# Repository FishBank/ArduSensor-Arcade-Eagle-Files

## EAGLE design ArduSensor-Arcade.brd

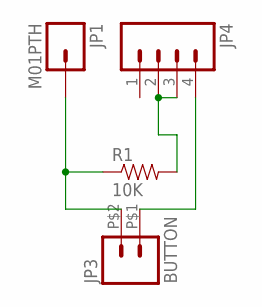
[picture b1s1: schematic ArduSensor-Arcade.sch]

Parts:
JP1: M01PTH; 1X01
JP3: BUTTON; 1X02_BIG
JP4: M04PTH; 1X04
R1: 10K; AXIAL-0.3

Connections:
unnamed: JP1.1, JP3.P$2 (2), R1.P$1 (1)
unnamed: JP4.2, JP4.3, R1.P$2 (2)
unnamed: JP3.P$1 (1), JP4.4

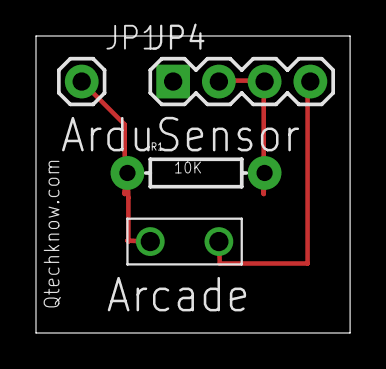
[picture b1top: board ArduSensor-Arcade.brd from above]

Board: 2 copper layers, 17.4 x 16.5 mm, 4 parts (0 on the bottom side), 3 nets.

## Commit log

2012-07-13 Schematic

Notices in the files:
parts and their libraries:
SFE Connectors: Licensing: CC v3.0 Share-Alike You are welcome to use this library for commercial purposes.
